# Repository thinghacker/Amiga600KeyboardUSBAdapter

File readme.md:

# Amiga600 Keyboard USB Adapter
This project enables an existing Amiga 600 Keyboard to operate as a USB Keyboard with the Case LEDs to indicate power/scroll lock and numlock.
This is a reimplementation of my previous [Teensy 2.0++ based PCB](https://github.com/thinghacker/amiga600_usb_pcb) and [QMK Firmware](https://github.com/thinghacker/qmk_firmware/tree/amiga600/keyboards/amiga600) adapter however as the Teensy 2.0++ is approaching end of sales availability and is relatively expensive,
this recreation uses the Raspberry Pi Pico in combination with a MCP20008 IO Expander for the keyboard interface and the keyboard driver software written in [CircuitPython](https://circuitpython.org/)

The [Kicad](https://www.kicad.org/) files used to create the PCB are in the [PCB-Amiga600Keyboard_USB_Pico](PCB-Amiga600Keyboard_USB_Pico/) directory - generated gerbers are the **plot** directory
The CircuitPython code is in the [CircuitPythonCode-Amiga600Keyboard_USB_Pico](CircuitPythonCode-Amiga600Keyboard_USB_Pico/) directory

Please note that the code requires the following libraries in addition to the base CircuitPython Install 
* [Adafruit_CircuitPython_HID](https://github.com/adafruit/Adafruit_CircuitPython_HID)
* [Adafruit_CircuitPython_MCP230xx](https://github.com/adafruit/Adafruit_CircuitPython_MCP230xx)

### Bill of Materials

|Designation              | Item    | Description | Manufacturer|
| ------------ | ------------ |------------ | ---------- |
| U1 | Raspberry Pi Pico | RP2040 Board with USB Connector | https://www.raspberrypi.org/products/raspberry-pi-pico/ | 
| U2 | MCP20008 | 8 bit I2C IO Expander | https://www.microchip.com/wwwproducts/en/MCP23008 | 
|J1|4 Pin Header Right Angle PCB Mount 2.54mm spacing|Connects to Amiga 600 Case LEDs|Sullins Connector Solutions SWR25X-NRTC-S04-RB-BA available from Jaycar as HM3424|
|J2|30 Pin FPC Connector 1.25mm spacing| Connects to the Amiga 600 Keyboard Ribbon|Molex 39532304|
|R1 & R2 |4K7 Ohm Resistor|Pullups for I2C|various|

### PCB
This is a fairly simple two layer through hole design.  There are holes in the PCB to accomodate 3mm Nylon standoffs, self-adhesive types mean you can attach it to the back of the keyboard if desired.

Assembled Prototype PCB

Assembled Prototype PCB connected to a Keyboard

### Construction Notes
This PCB does not require any advanced soldering skills, it may be best to work with an experienced friend or watch some youtube videos on build techniques if you don't feel confident.

The hardware and software as written by me is distributed under a GPL Version 3 License

No claims to the name or any trademarks associated with Amiga, Raspberry Pi, Pico or Tim Tam are asserted here.

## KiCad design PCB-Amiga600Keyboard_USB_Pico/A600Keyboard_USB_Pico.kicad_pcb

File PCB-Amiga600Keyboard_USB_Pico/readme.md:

# Amiga600 Keyboard USB Adapter Using a Raspberry Pi Pico and MCP20008
This Kicad 5.1.10 project enables an existing Amiga 600 Keyboard to be USB enabled via a Raspberry Pi Pico and MCP20008 with the appropriate firmware such as [This CircuitPython Firmware](https://github.com/thinghacker/Amiga600KeyboardUSBAdapter/tree/main/CircuitPythonCode-Amiga600Keyboard_USB_Pico)

The hardware design open and distributed under a GPL Version 3 License

[Here is a PDF of the schematic for reference](schematic.pdf)

Gerbers have already been generated and are present in the "plot" directory

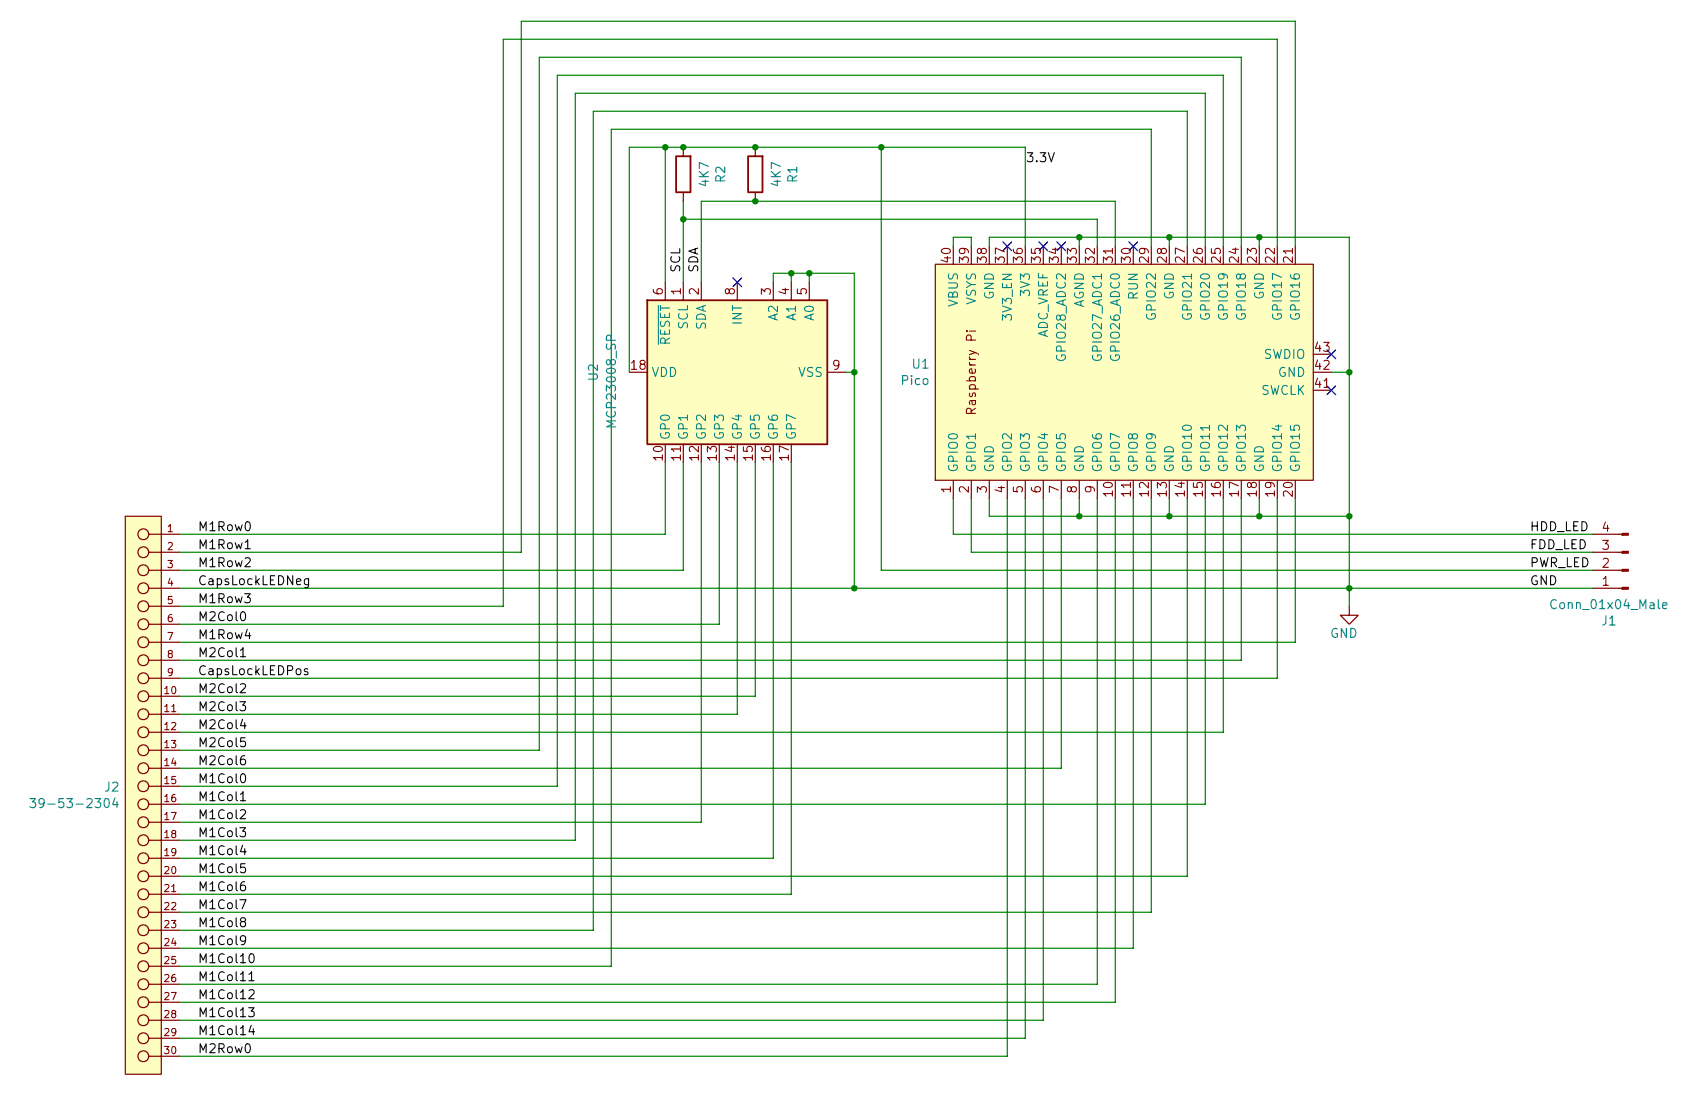
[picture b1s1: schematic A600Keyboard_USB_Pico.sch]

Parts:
J1: Conn_01x04_Male; PinHeader_1x04_P2.54mm_Horizontal
J2: 39-53-2304; Molex-39-53-2304-Manufacturer_Recommended; Voltage Max 200V
R1, R2: 4K7; R_Axial_DIN0207_L6.3mm_D2.5mm_P10.16mm_Horizontal
U1: Pico; RPi_Pico_SMD_TH
U2: MCP23008_SP; DIP-18_W7.62mm

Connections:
/3.3V: J1.2, R1.2, R2.2, U1.36 (3V3), U2.6 (~RESET), U2.18 (VDD)
/CapsLockLEDPos: J2.9, U1.19 (GPIO14)
/FDD_LED: J1.3, U1.2 (GPIO1)
/HDD_LED: J1.4, U1.1 (GPIO0)
/M1Col0: J2.15, U1.25 (GPIO19)
/M1Col1: J2.16, U1.15 (GPIO11)
/M1Col2: J2.17, U2.12 (GP2)
/M1Col3: J2.18, U1.26 (GPIO20)
/M1Col4: J2.19, U2.16 (GP6)
/M1Col5: J2.20, U1.14 (GPIO10)
/M1Col6: J2.21, U2.17 (GP7)
/M1Col7: J2.22, U1.12 (GPIO9)
/M1Col8: J2.23, U1.27 (GPIO21)
/M1Col9: J2.24, U1.11 (GPIO8)
/M1Col10: J2.25, U1.29 (GPIO22)
/M1Col11: J2.26, U1.9 (GPIO6)
/M1Col12: J2.27, U1.10 (GPIO7)
/M1Col13: J2.28, U1.6 (GPIO4)
/M1Col14: J2.29, U1.5 (GPIO3)
/M1Row0: J2.1, U2.10 (GP0)
/M1Row1: J2.2, U1.21 (GPIO16)
/M1Row2: J2.3, U2.11 (GP1)
/M1Row3: J2.5, U1.22 (GPIO17)
/M1Row4: J2.7, U1.20 (GPIO15)
/M2Col0: J2.6, U2.13 (GP3)
/M2Col1: J2.8, U1.17 (GPIO13)
/M2Col2: J2.10, U2.15 (GP5)
/M2Col3: J2.11, U2.14 (GP4)
/M2Col4: J2.12, U1.16 (GPIO12)
/M2Col5: J2.13, U1.24 (GPIO18)
/M2Col6: J2.14, U1.7 (GPIO5)
/M2Row0: J2.30, U1.4 (GPIO2)
/SCL: R2.1, U1.32 (GPIO27_ADC1), U2.1 (SCL)
/SDA: R1.1, U1.31 (GPIO26_ADC0), U2.2 (SDA)
GND: J1.1, J2.4, U1.3 (GND), U1.8 (GND), U1.13 (GND), U1.18 (GND), U1.23 (GND), U1.28 (GND), U1.33 (AGND), U1.38 (GND), U1.42 (GND), U2.3 (A2), U2.4 (A1), U2.5 (A0), U2.9 (VSS)
unnamed: U1.39 (VSYS), U1.40 (VBUS)

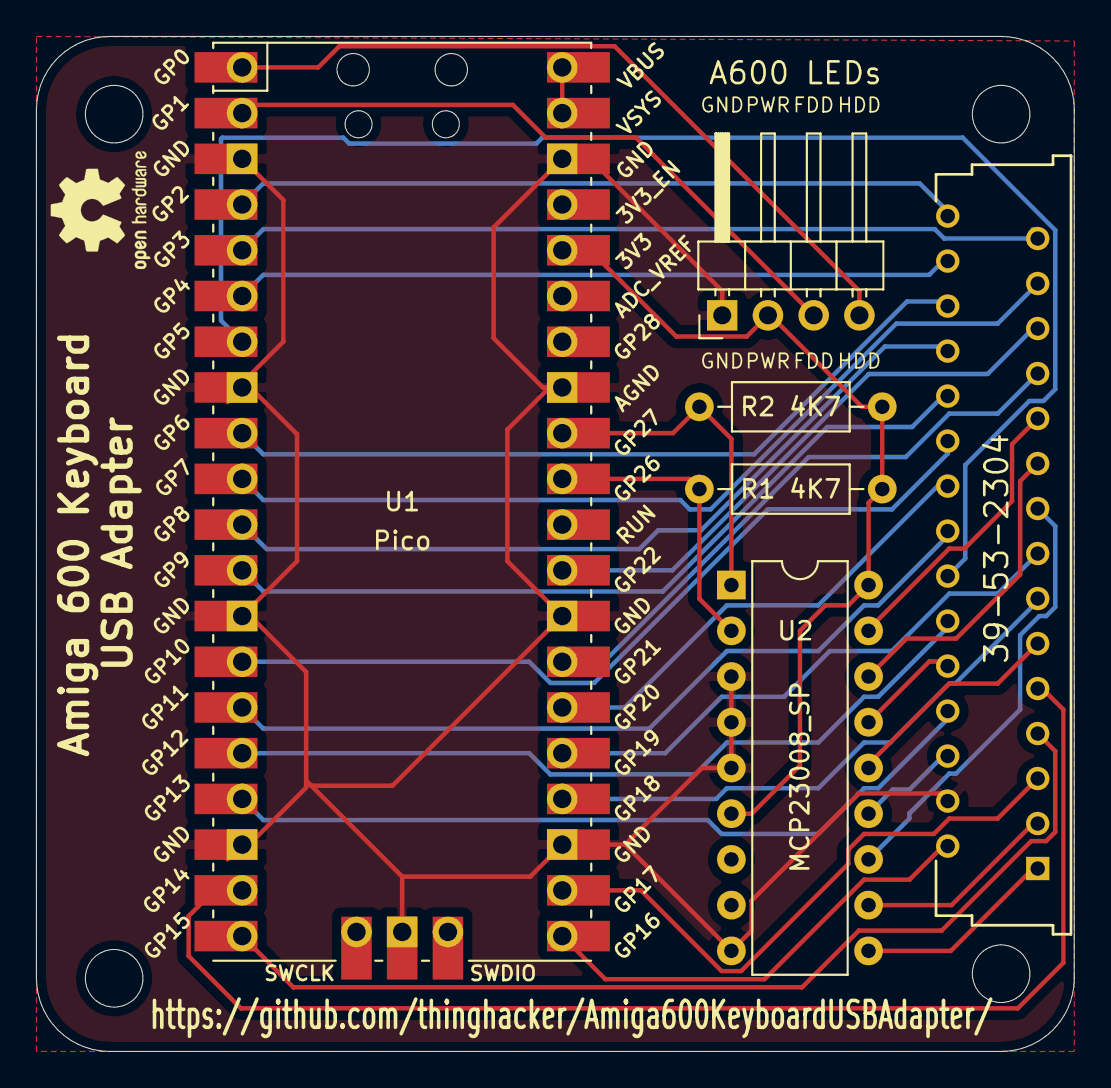
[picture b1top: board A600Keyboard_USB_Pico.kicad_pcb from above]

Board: 2 copper layers, 57.7 x 56.4 mm, 6 parts (0 on the bottom side), 36 nets.

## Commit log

2021-07-09 First Release
2021-07-10 Back Silk Screen Correction
2021-07-10 Attempting to be clearer in the build instructions
2025-08-13 Update code.py - initial delay to avoid initial detection problem
    Fix provided by Amellinium 12-Aug-25
2025-08-13 Create boot.py - enable only required USB functionality
    Fix provided by n0rt0nthec4t 11-May-23
